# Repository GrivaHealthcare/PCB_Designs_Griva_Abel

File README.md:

# PCB_Designs_Griva_Abel
PCB designs for the subsidary boards

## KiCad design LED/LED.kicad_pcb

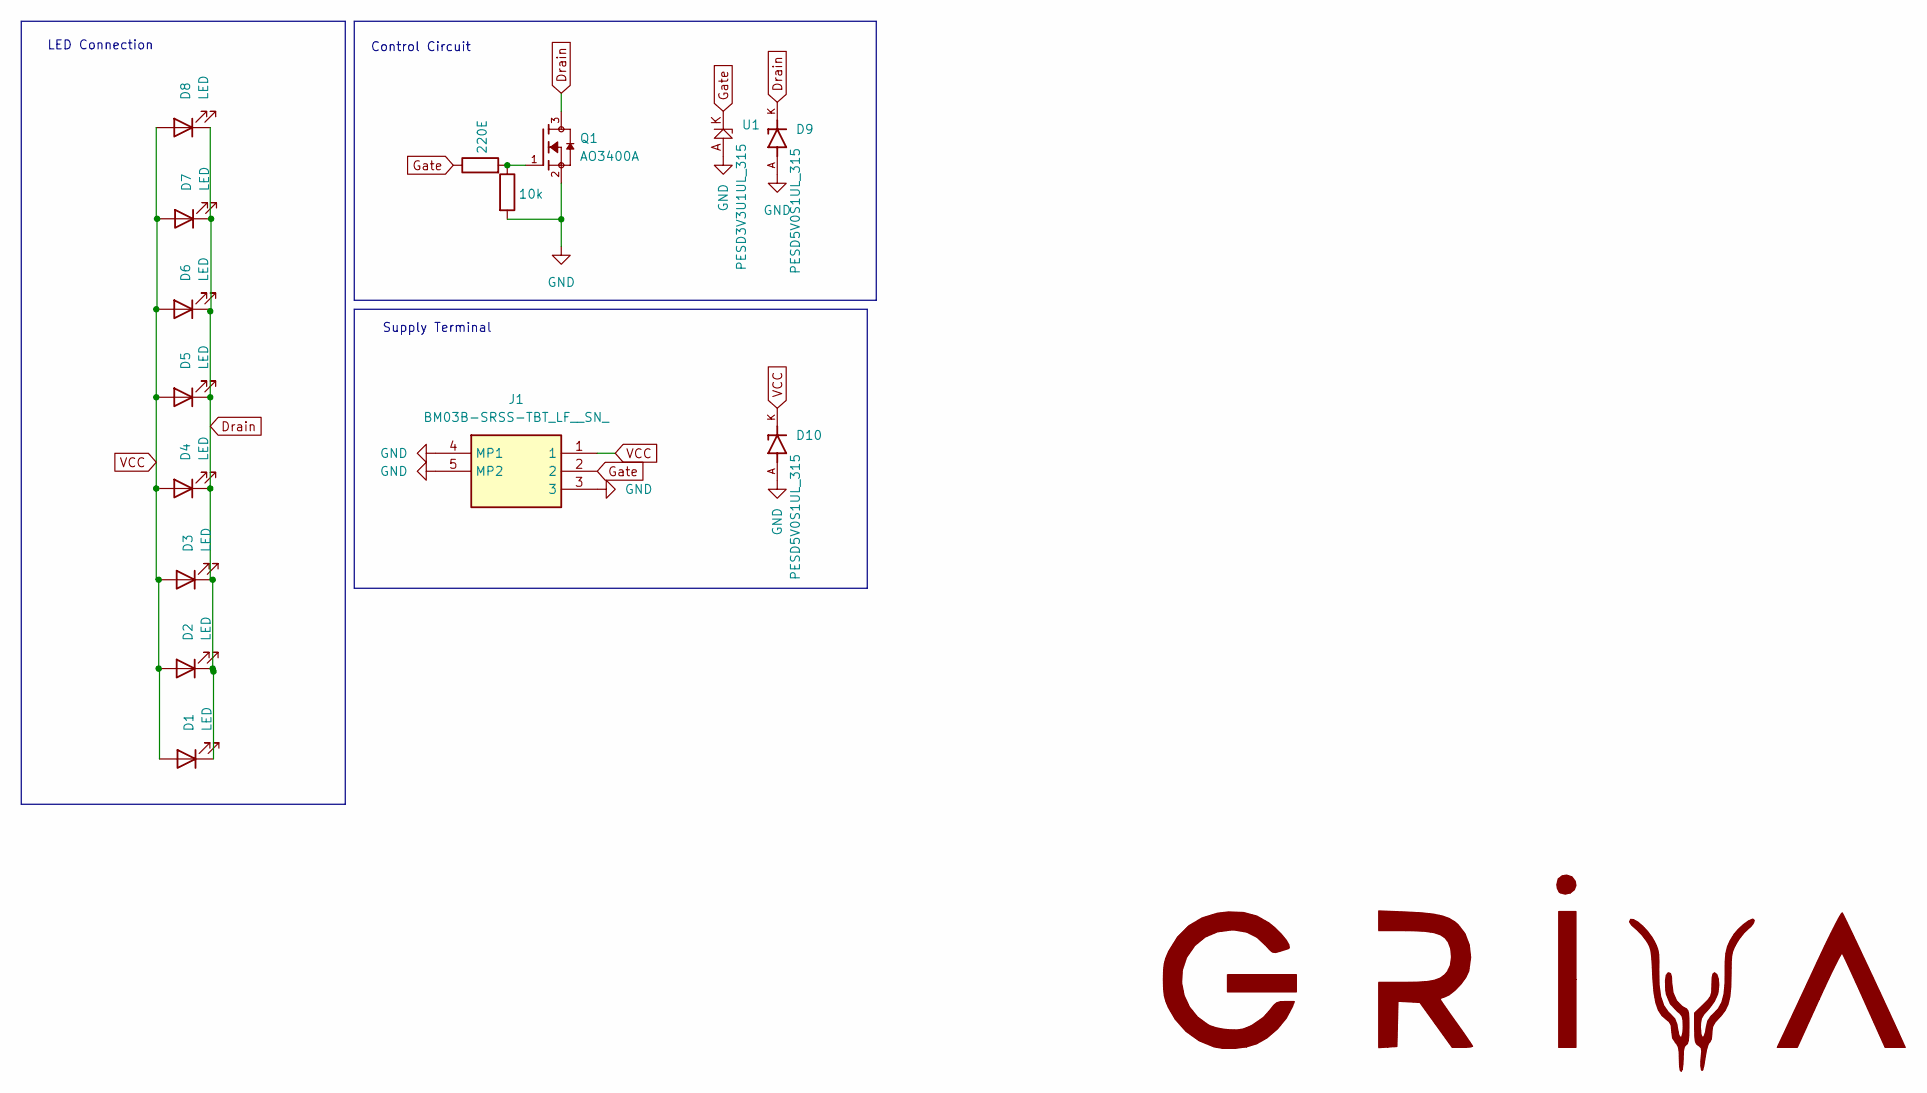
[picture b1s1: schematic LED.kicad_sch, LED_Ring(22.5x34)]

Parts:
D1, D2, D3, D4, D5, D6, D7, D8: LED; LED_Sunrom
D9, D10: PESD5V0S1UL_315; DIO_PESD5V0S1UL_315
J1: BM03B-SRSS-TBT_LF__SN_; BM03BSRSSTBTLFSN; Mouser Part Number N/A
Q1: AO3400A; SOT-23-3L_AOS-L; PARTREV L
R1: 10k; R_0402_1005Metric_Pad0.72x0.64mm_HandSolder
R2: 220E; R_0402_1005Metric_Pad0.72x0.64mm_HandSolder
U1: PESD3V3U1UL_315; DIO_PESD5V0S1UL_315

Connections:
Drain: D1.1 (K), D2.1 (K), D3.1 (K), D4.1 (K), D5.1 (K), D6.1 (K), D7.1 (K), D8.1 (K), D9.K, Q1.3
GND: D9.A, D10.A, J1.3, J1.4 (MP1), J1.5 (MP2), Q1.2, R1.2, U1.A
Gate: J1.2, R2.1, U1.K
unnamed: Q1.1, R1.1, R2.2
VCC: D1.2 (A), D2.2 (A), D3.2 (A), D4.2 (A), D5.2 (A), D6.2 (A), D7.2 (A), D8.2 (A), D10.K, J1.1

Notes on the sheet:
Supply Terminal
Control Circuit
LED Connection

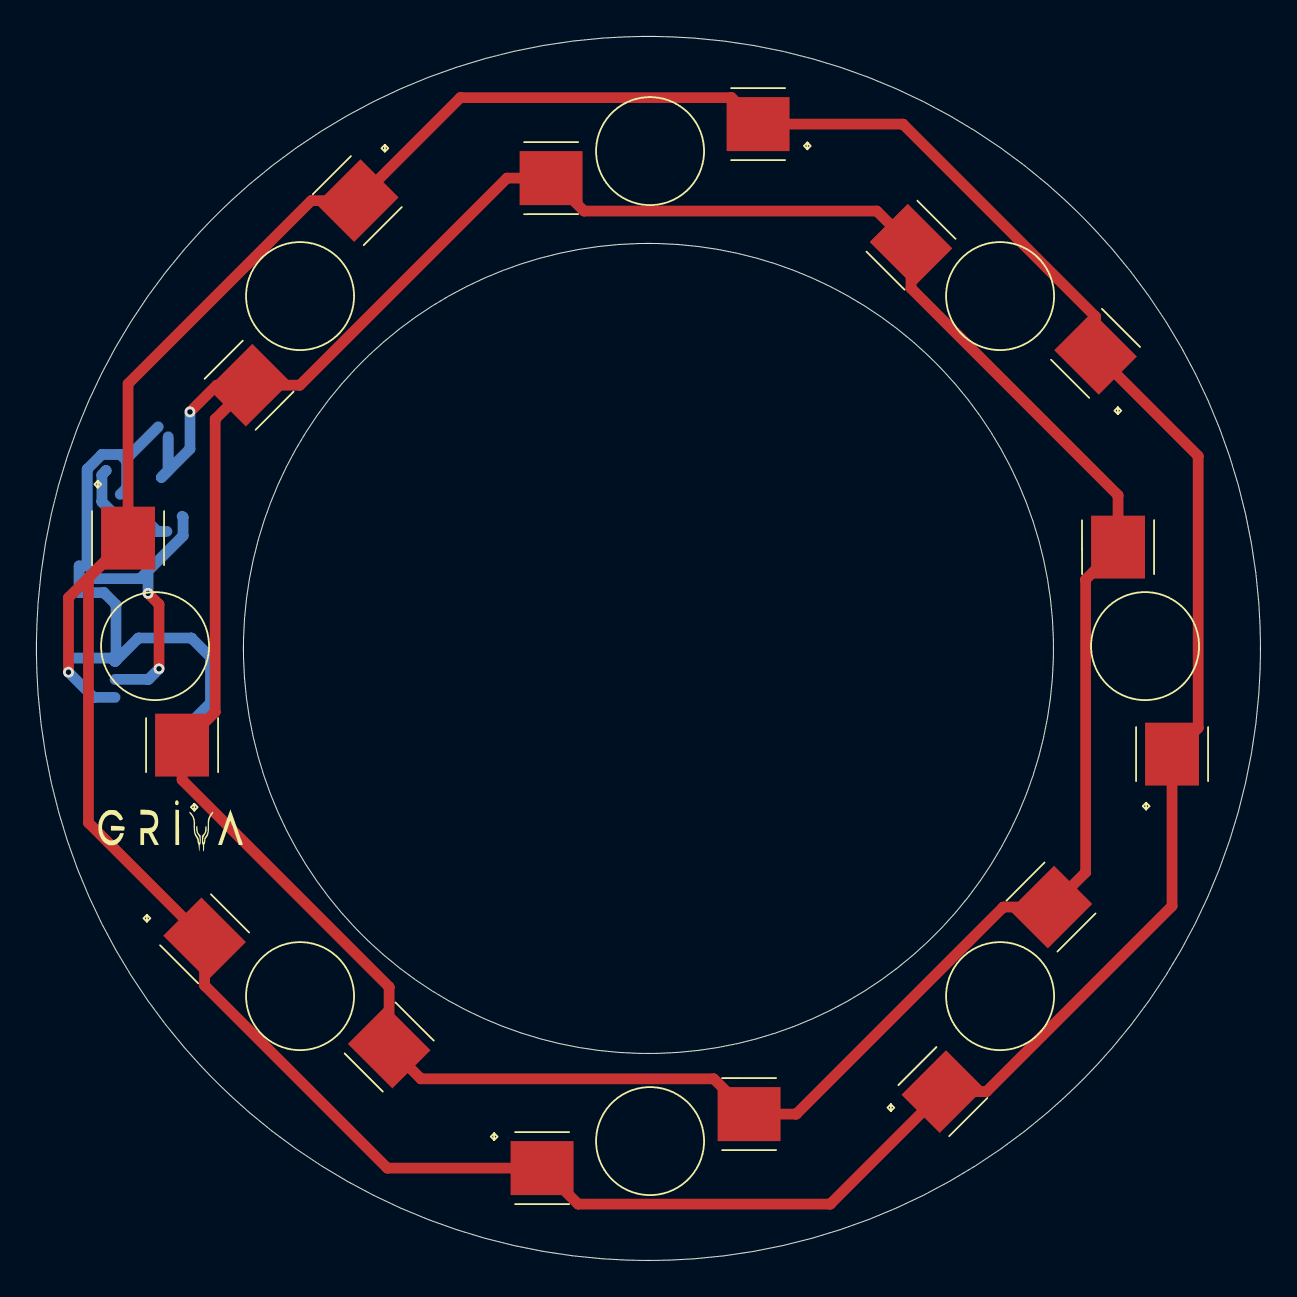
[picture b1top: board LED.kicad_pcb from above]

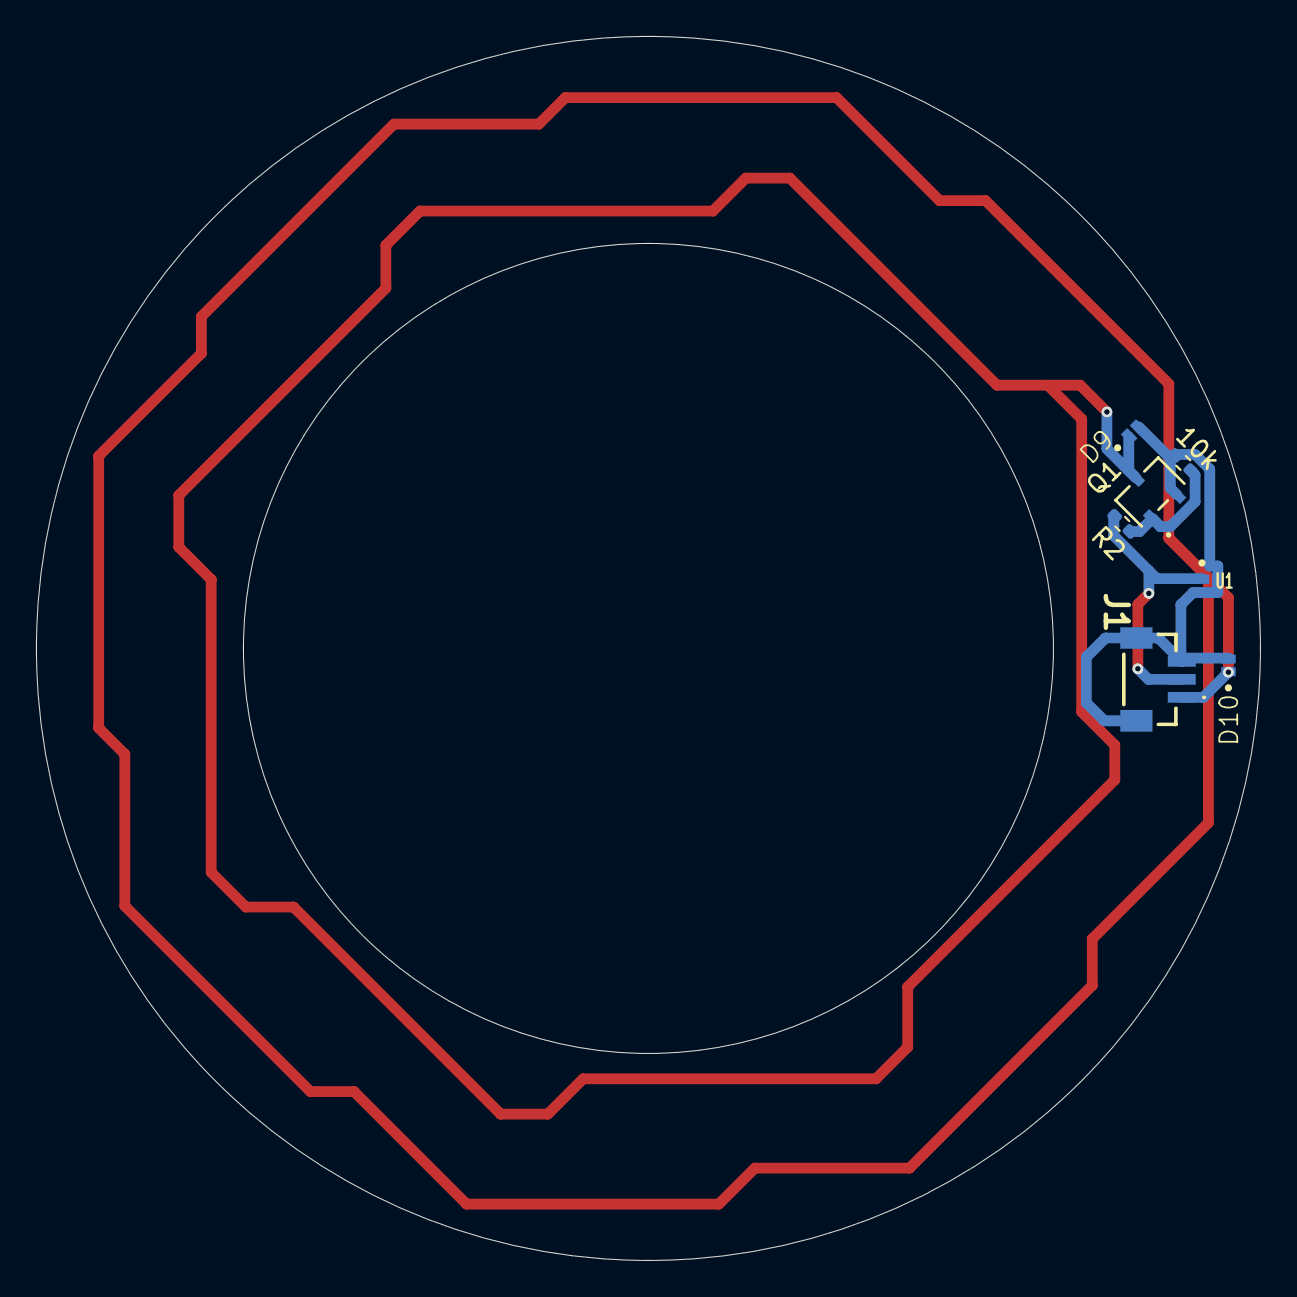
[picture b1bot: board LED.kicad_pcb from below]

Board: 2 copper layers, 68.0 x 68.0 mm, 15 parts (7 on the bottom side), 5 nets.

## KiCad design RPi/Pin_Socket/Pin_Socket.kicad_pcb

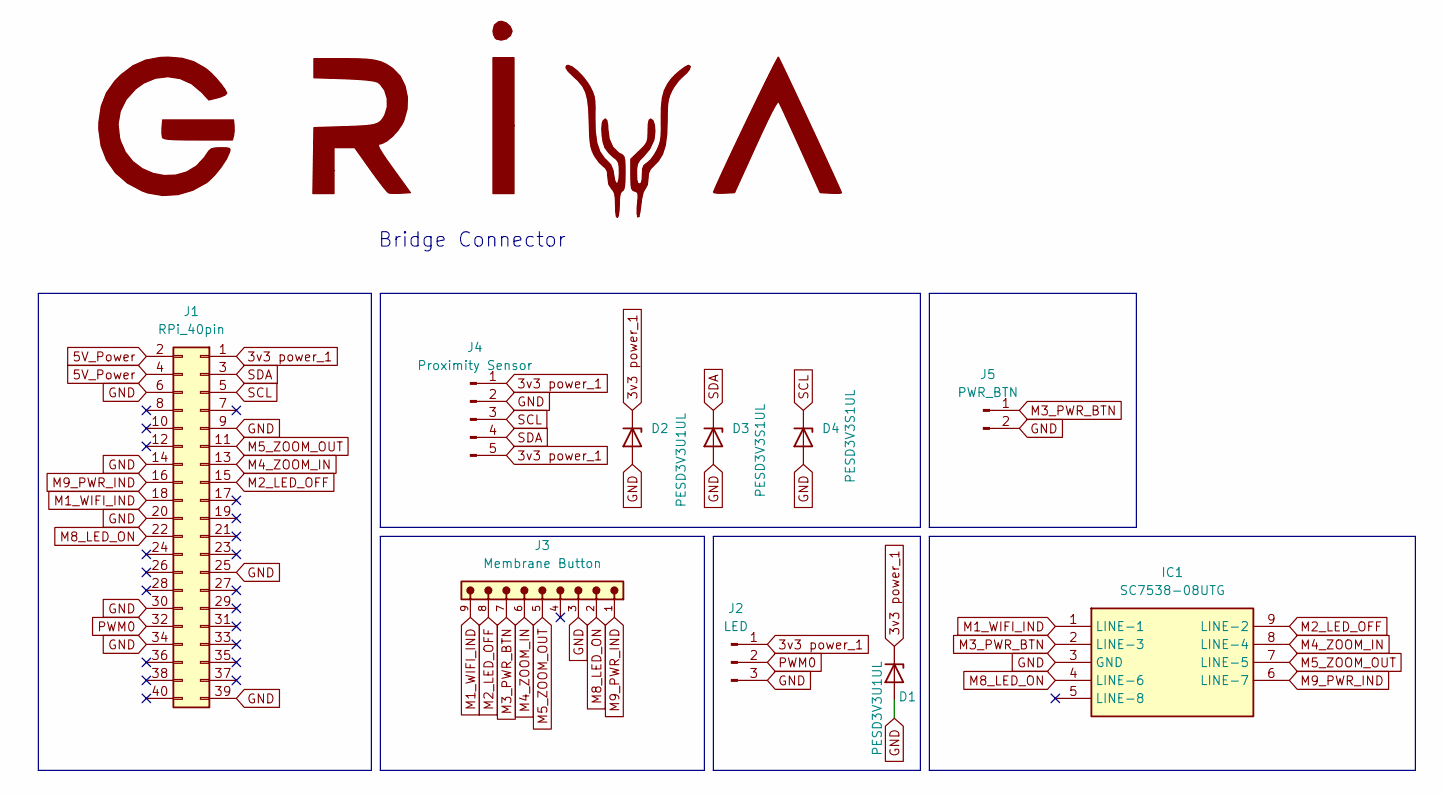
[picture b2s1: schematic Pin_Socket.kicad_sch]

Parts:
D1, D2: PESD3V3U1UL; D_SOD-882
D3, D4: PESD3V3S1UL; D_SOD-882
IC1: SC7538-08UTG; SC753808UTG; Manufacturer_Part_Number SC7538-08UTG; Mouser Part Number 576-SC7538-08UTG
J1: RPi_40pin; PinSocket_2x20_P2.54mm_Vertical
J2: LED; LED 3pin
J3: Membrane Button; 61300911121
J4: Proximity Sensor; Prox_5pin
J5: PWR_BTN

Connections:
3v3 power_1: D1.1 (K), D2.1 (K), J1.1, J2.1, J4.1, J4.5
5V_Power: J1.2, J1.4
GND: D1.2 (A), D2.2 (A), D3.2 (A), D4.2 (A), IC1.3 (GND), J1.6, J1.9, J1.14, J1.20, J1.25, J1.30, J1.34, J1.39, J2.3, J3.3, J4.2, J5.2
M1_WIFI_IND: IC1.1 (LINE-1), J1.18, J3.9
M2_LED_OFF: IC1.9 (LINE-2), J1.15, J3.8
M3_PWR_BTN: IC1.2 (LINE-3), J3.7, J5.1
M4_ZOOM_IN: IC1.8 (LINE-4), J1.13, J3.6
M5_ZOOM_OUT: IC1.7 (LINE-5), J1.11, J3.5
M8_LED_ON: IC1.4 (LINE-6), J1.22, J3.2
M9_PWR_IND: IC1.6 (LINE-7), J1.16, J3.1
PWM0: J1.32, J2.2
SCL: D4.1 (K), J1.5, J4.3
SDA: D3.1 (K), J1.3, J4.4

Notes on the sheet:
Bridge Connector

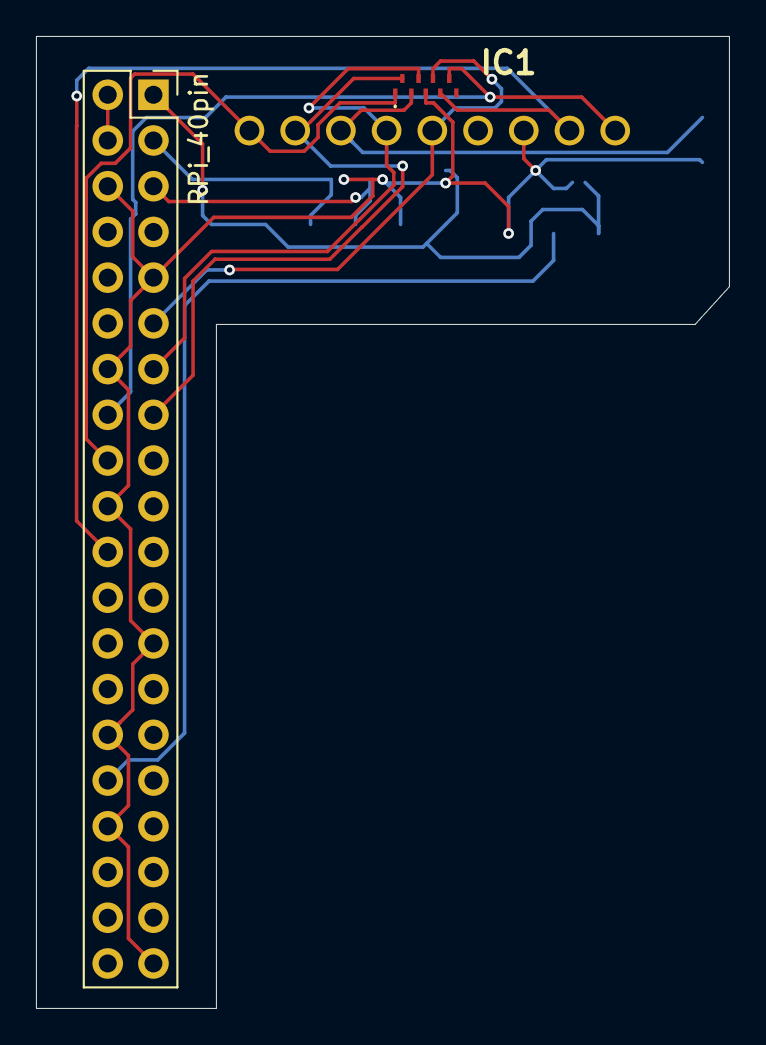
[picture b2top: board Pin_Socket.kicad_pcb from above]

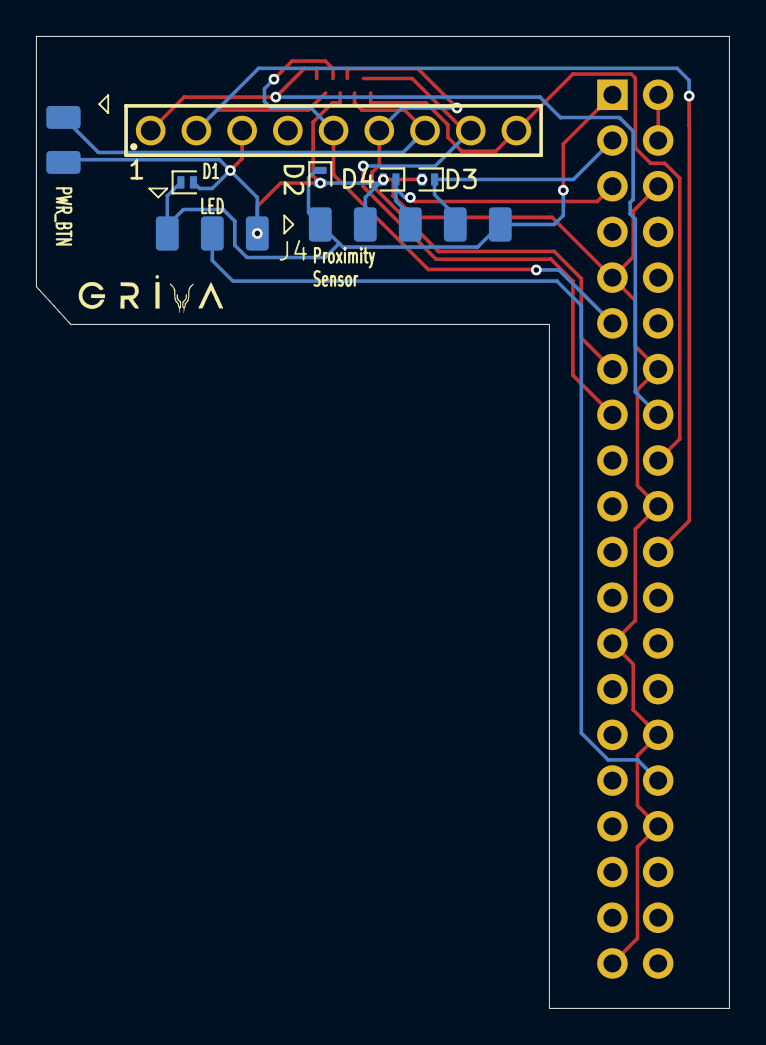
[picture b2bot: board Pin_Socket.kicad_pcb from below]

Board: 2 copper layers, 38.5 x 54.0 mm, 10 parts (8 on the bottom side), 13 nets.

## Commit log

2026-01-05 Pin Socket board for Proximity,LED ring, and Membrane Switch
2026-01-05 LED ring PCB files
2026-01-05 changed footprint for proper placement of components
2026-01-05 a 3d file for the LED Luminax_led.step
2026-01-05 LED Ring BOM
2026-01-05 Bridge board BOM
